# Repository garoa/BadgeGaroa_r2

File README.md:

A documentação desse projeto se encontra em https://garoa.net.br/wiki/Badge#REV._0

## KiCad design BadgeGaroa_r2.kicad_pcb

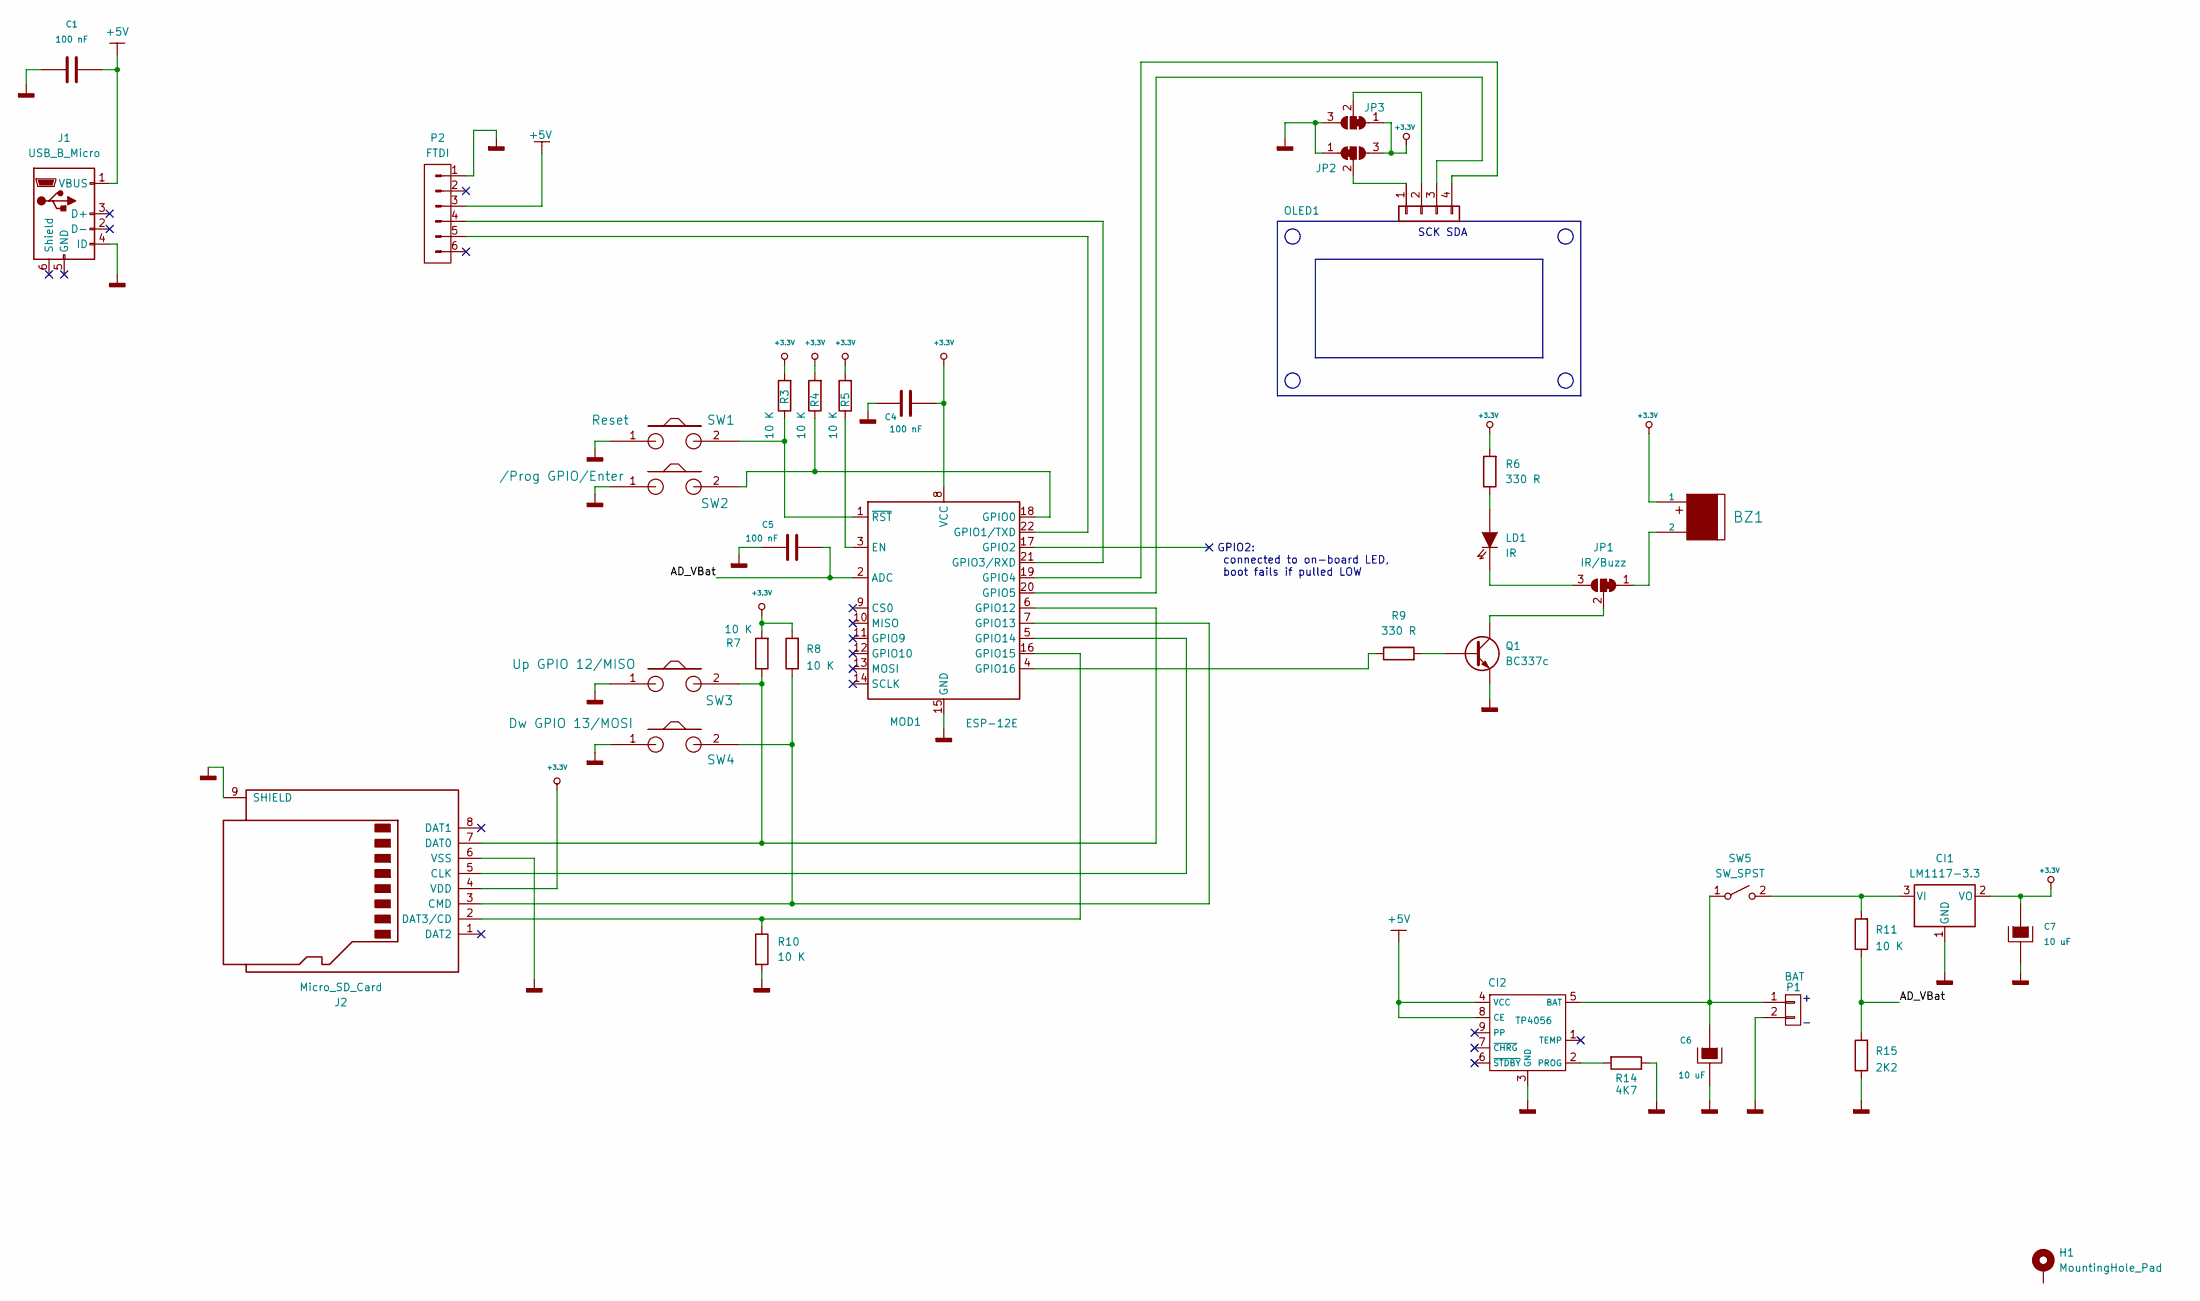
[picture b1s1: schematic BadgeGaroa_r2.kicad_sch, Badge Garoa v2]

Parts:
BZ1: BUZZER MLT-8530; MagneticBuzzer_Kobitone_254-EMB84Q-RO
C1, C4, C5: 100 nF; C_Disc_D4.3mm_W1.9mm_P5.00mm
C6, C7: 10 uF; CP_Radial_D5.0mm_P2.50mm
CI1: LM1117-3.3; SOT-223
CI2: TP4056; SOIC-8-1EP_3.9x4.9mm_P1.27mm_EP2.29x3mm
H1: MountingHole_Pad; MountingHole_6.4mm_M6_ISO14580_Pad_TopBottom
J1: USB_B_Micro; usb-PCB
J2: Micro_SD_Card; microSD_HC_iivverr _sharvielectronics.Generic
JP1, JP2, JP3: IR/Buzz; SolderJumper-3_P1.3mm_Bridged12_Pad1.0x1.5mm
LD1: IR; LED_D5.0mm_Horizontal_O1.27mm_Z3.0mm_Clear
MOD1: ESP-12E
OLED1: Conn_01x04; PinHeader_1x04_P2.54mm_Vertical
P1: BAT; PinHeader_1x02_P2.54mm_Vertical
P2: FTDI; CON6ICSP
Q1: BC337c; TO-92L
R3, R4, R5, R7, R8, R10, R11: 10 K; R_Axial_DIN0204_L3.6mm_D1.6mm_P7.62mm_Horizontal
R6, R9: 330 R; R_Axial_DIN0204_L3.6mm_D1.6mm_P7.62mm_Horizontal
R14: 4K7; R_Axial_DIN0204_L3.6mm_D1.6mm_P7.62mm_Horizontal
R15: 2K2; R_Axial_DIN0204_L3.6mm_D1.6mm_P7.62mm_Horizontal
SW1: Reset; SW_SPST_CK_RS282G05A3
SW2: /Prog GPIO/Enter; SW_SPST_CK_RS282G05A3
SW3: Up GPIO 12/MISO; SW_SPST_CK_RS282G05A3
SW4: Dw GPIO 13/MOSI; SW_SPST_CK_RS282G05A3
SW5: SW_SPST; SW_SPDT_CK_JS102011SAQN

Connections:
+3.3V: BZ1.1, C4.2, C7.1, CI1.2 (VO), J2.4 (VDD), JP2.3 (B), JP3.1 (A), MOD1.8 (VCC), R3.2, R4.2, R5.2, R6.2, R7.2, R8.2
+5V: C1.2, CI2.4 (VCC), CI2.8 (CE), J1.1 (VBUS), P2.3
/AD_VBat: C5.2, MOD1.2 (ADC), R11.1, R15.2
GNDD: C1.1, C4.1, C5.1, C6.2, C7.2, CI1.1 (GND), CI2.3 (GND), J1.4 (ID), J2.6 (VSS), J2.9 (SHIELD), JP2.1 (A), JP3.3 (B), MOD1.15 (GND), P1.2, P2.1, Q1.3 (E), R10.2, R14.1, R15.1, SW1.1, SW2.1, SW3.1, SW4.1
unnamed: CI1.3 (VI), R11.2, SW5.2 (B)
unnamed: C6.1, CI2.5 (BAT), P1.1, SW5.1 (A)
unnamed: CI2.2 (PROG), R14.2
unnamed: J2.5 (CLK), MOD1.5 (GPIO14)
unnamed: J2.3 (CMD), MOD1.7 (GPIO13), R8.1, SW4.2
unnamed: J2.7 (DAT0), MOD1.6 (GPIO12), R7.1, SW3.2
unnamed: J2.2 (DAT3/CD), MOD1.16 (GPIO15), R10.1
unnamed: BZ1.2, JP1.1 (A)
unnamed: JP1.3 (B), LD1.2 (K)
unnamed: JP1.2 (C), Q1.1 (C)
unnamed: JP2.2 (C), OLED1.1
unnamed: JP3.2 (C), OLED1.2
unnamed: LD1.1 (A), R6.1
unnamed: MOD1.3 (EN), R5.1
unnamed: MOD1.18 (GPIO0), R4.1, SW2.2
unnamed: MOD1.22 (GPIO1/TXD), P2.5
unnamed: MOD1.21 (GPIO3/RXD), P2.4
unnamed: MOD1.19 (GPIO4), OLED1.4
unnamed: MOD1.20 (GPIO5), OLED1.3
unnamed: MOD1.4 (GPIO16), R9.1
unnamed: MOD1.1 (~RST), R3.1, SW1.2
unnamed: Q1.2 (B), R9.2

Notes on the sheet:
+ -
SCK SDA
GPIO2: connected to on-board LED, boot fails if pulled LOW

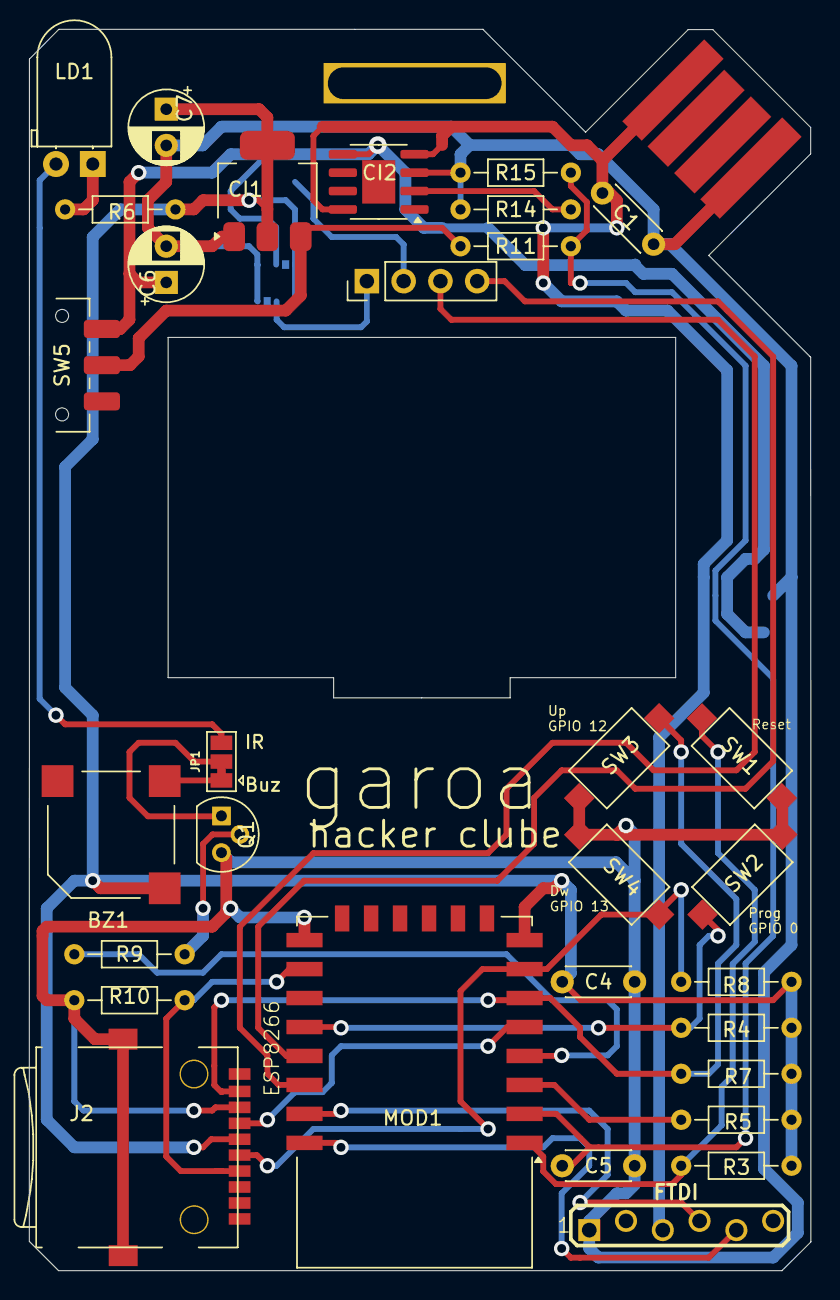
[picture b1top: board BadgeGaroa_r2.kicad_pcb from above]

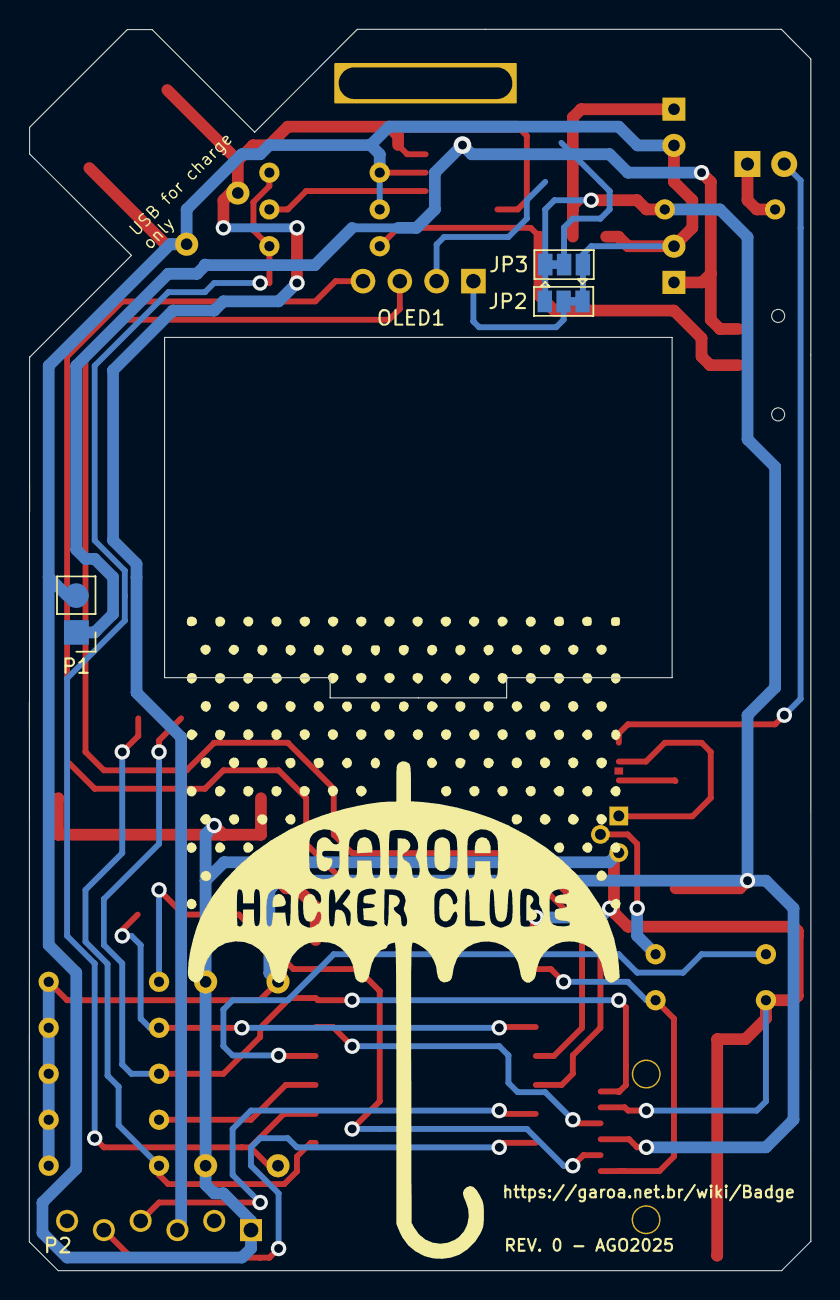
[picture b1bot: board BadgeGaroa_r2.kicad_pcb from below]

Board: 2 copper layers, 54.0 x 85.7 mm, 36 parts (3 on the bottom side), 26 nets.

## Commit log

2025-10-22 Reorganizando o repositório e adicionando alguns scripts
2025-10-24 Adicionar teste do arduino e mais deletand arquivos repetidos
2025-10-24 Adicionado binários
2025-10-25 Atualizações
